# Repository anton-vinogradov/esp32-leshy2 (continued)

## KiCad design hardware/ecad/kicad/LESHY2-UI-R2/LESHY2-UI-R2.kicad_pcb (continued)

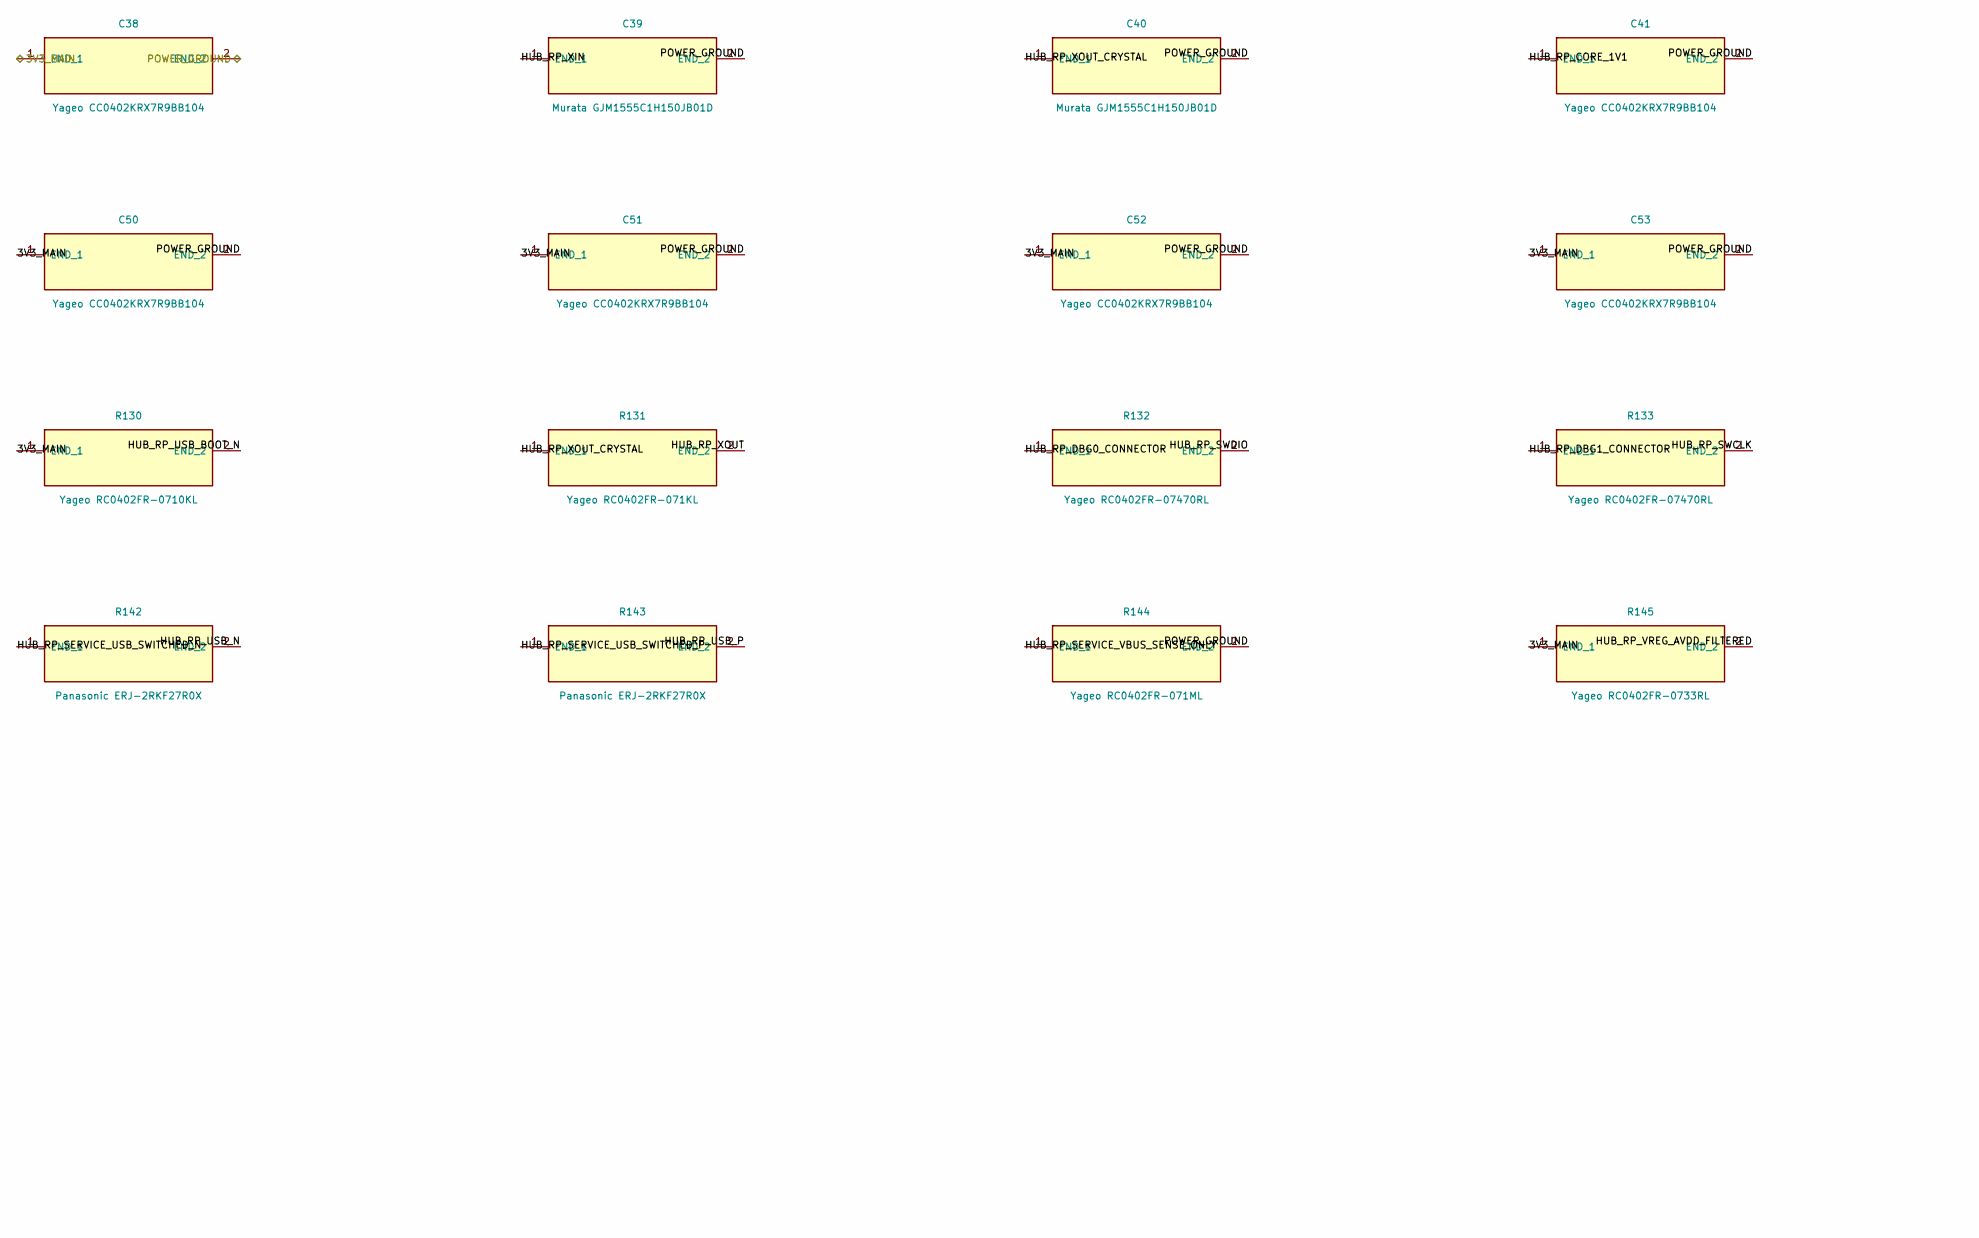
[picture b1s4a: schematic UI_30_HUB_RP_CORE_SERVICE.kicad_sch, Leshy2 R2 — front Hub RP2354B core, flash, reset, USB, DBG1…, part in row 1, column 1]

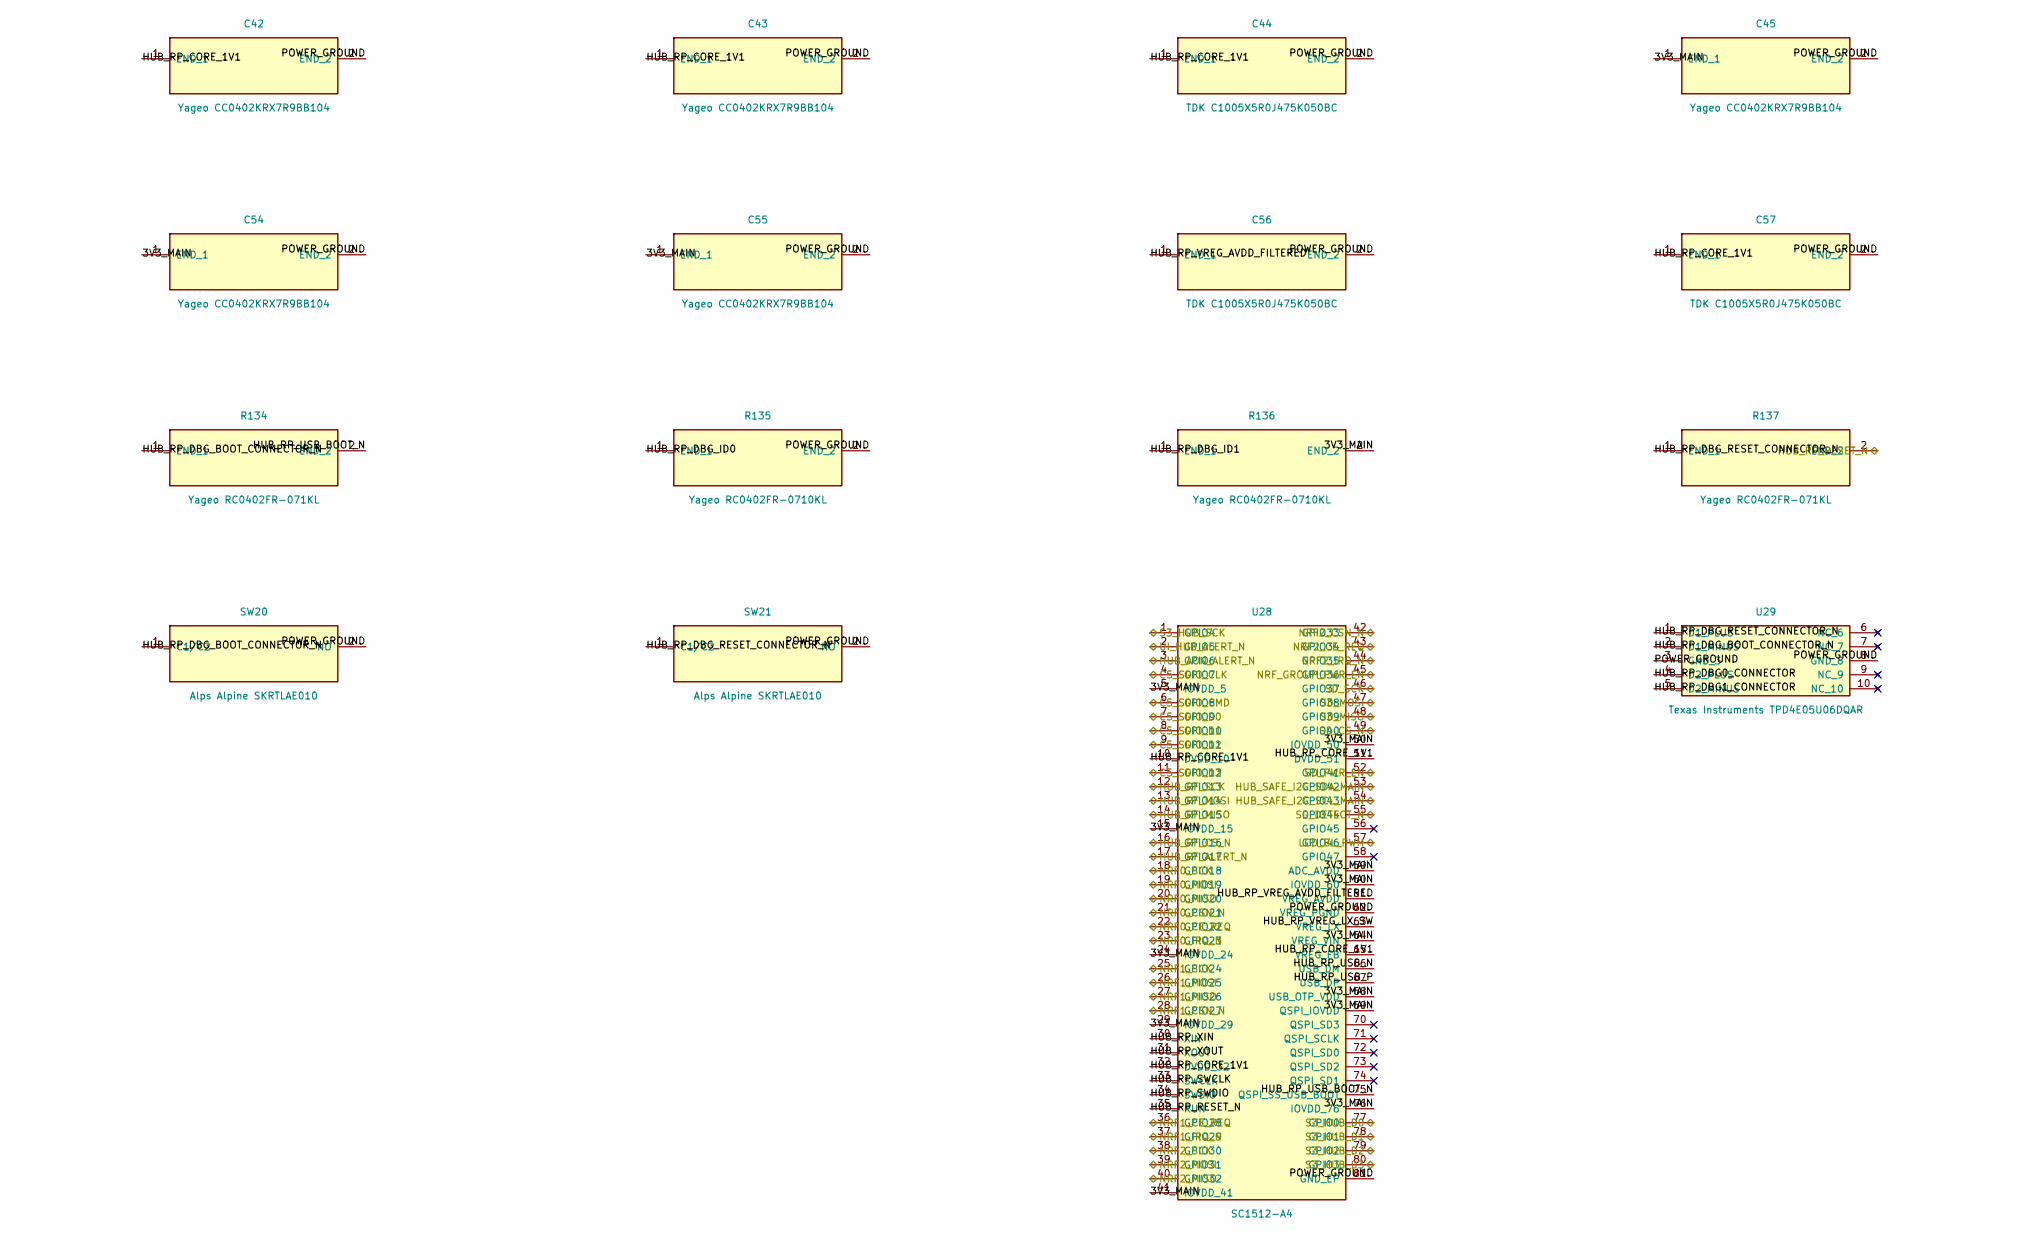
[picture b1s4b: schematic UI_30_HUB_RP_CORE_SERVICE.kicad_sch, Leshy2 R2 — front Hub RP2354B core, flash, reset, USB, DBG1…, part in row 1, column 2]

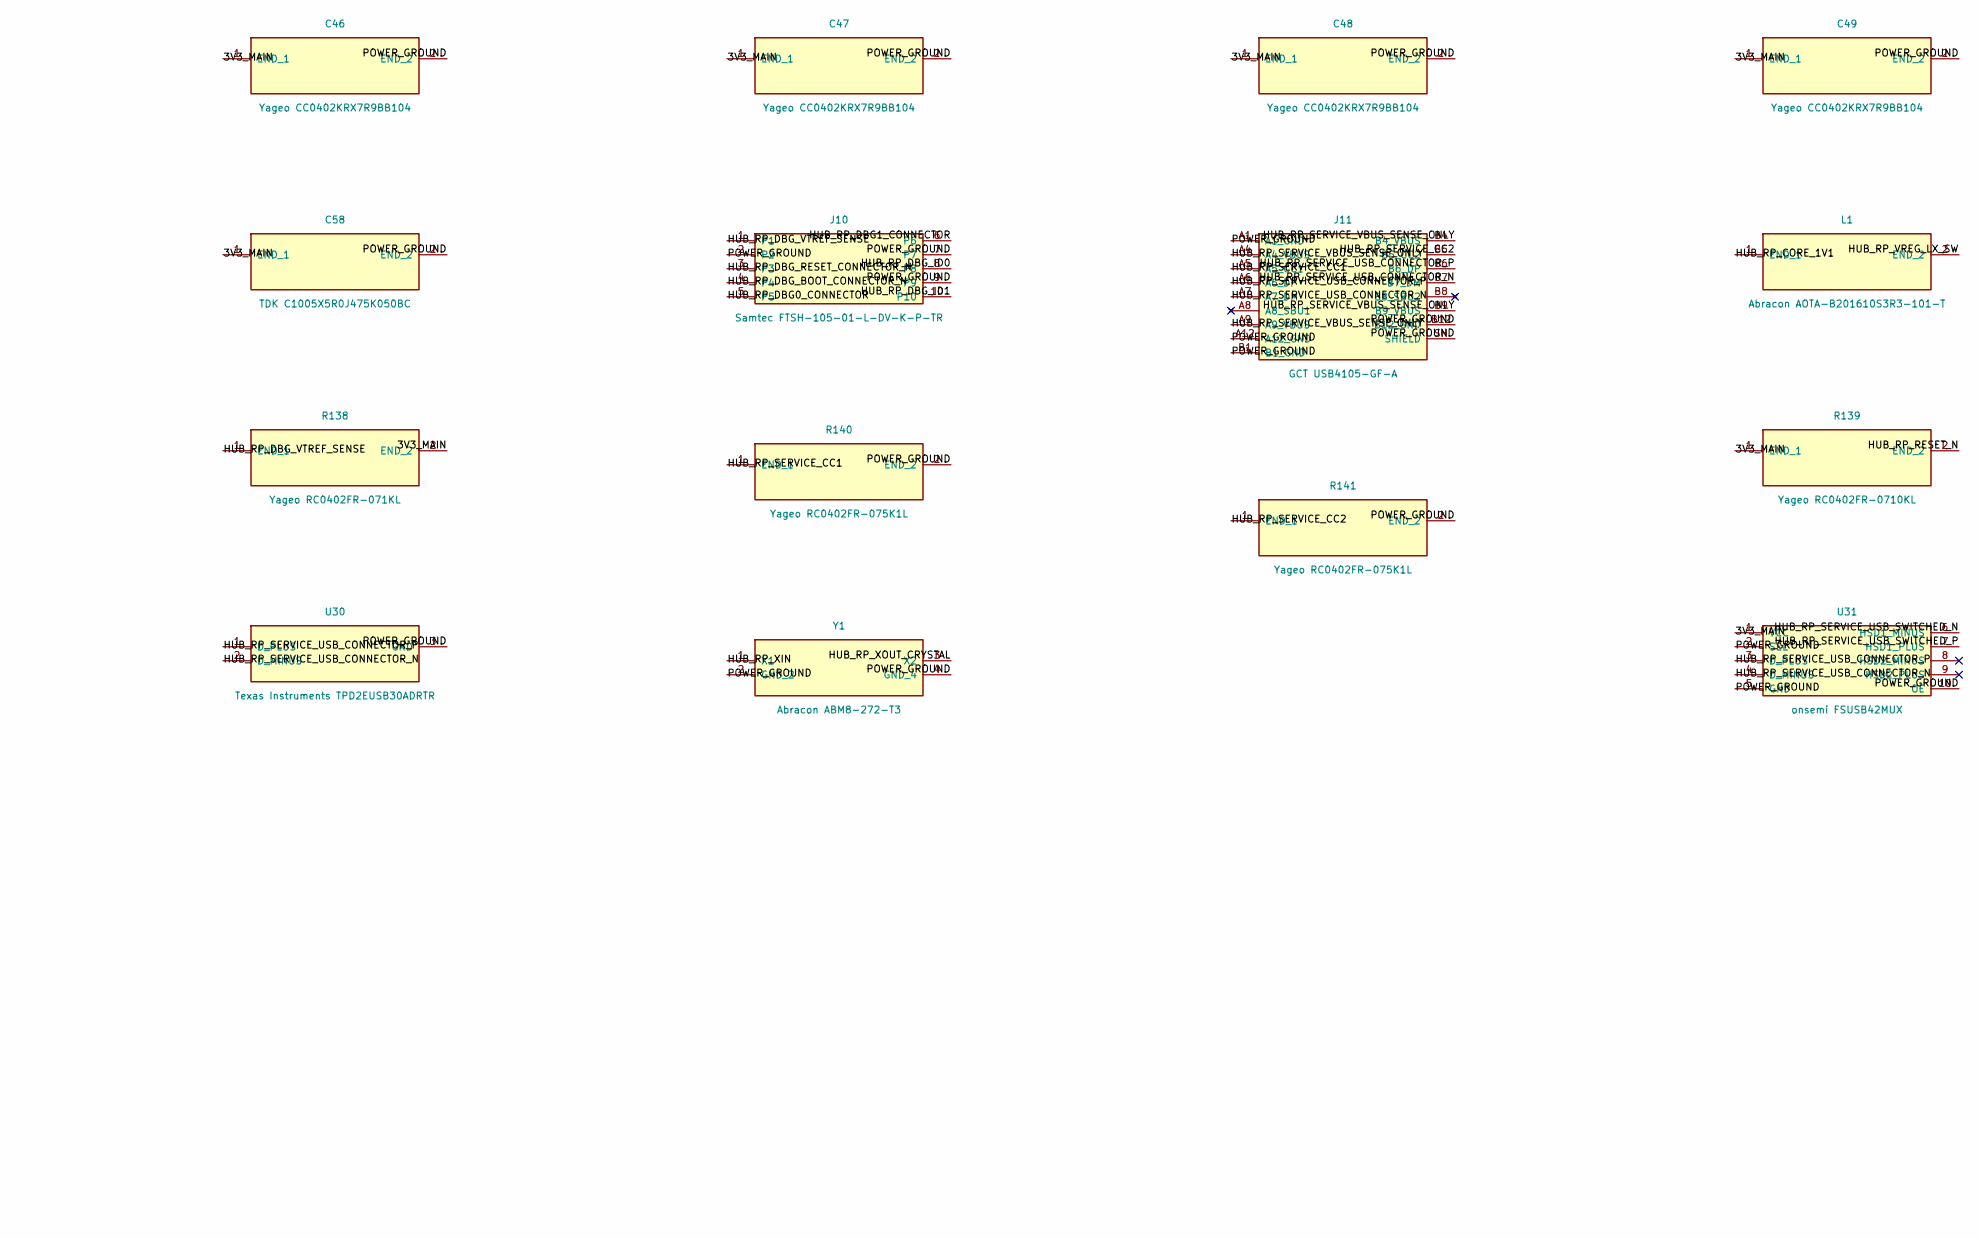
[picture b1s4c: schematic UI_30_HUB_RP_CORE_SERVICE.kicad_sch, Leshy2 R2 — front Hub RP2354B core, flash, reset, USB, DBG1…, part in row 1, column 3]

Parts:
C38, C41, C42, C43, C45, C46, C47, C48, C49, C50, C51, C52, C53, C54, C55: Yageo CC0402KRX7R9BB104; C_0402_1005Metric
C39, C40: Murata GJM1555C1H150JB01D; C_0402_1005Metric
C44, C56, C57, C58: TDK C1005X5R0J475K050BC; C_0402_1005Metric
J10: Samtec FTSH-105-01-L-DV-K-P-TR; FTSH-105-01-L-DV-K-P-TR
J11: GCT USB4105-GF-A; USB_C_Receptacle_GCT_USB4105-xx-A_16P_TopMnt_Horizontal
L1: Abracon AOTA-B201610S3R3-101-T; L_Murata_DFE201610P
R130, R135, R136, R139: Yageo RC0402FR-0710KL; R_0402_1005Metric
R131, R134, R137, R138: Yageo RC0402FR-071KL; R_0402_1005Metric
R132, R133: Yageo RC0402FR-07470RL; R_0402_1005Metric
R140, R141: Yageo RC0402FR-075K1L; R_0402_1005Metric
R142, R143: Panasonic ERJ-2RKF27R0X; R_0402_1005Metric
R144: Yageo RC0402FR-071ML; R_0402_1005Metric
R145: Yageo RC0402FR-0733RL; R_0402_1005Metric
SW20, SW21: Alps Alpine SKRTLAE010; SW_Push_1P1T-MP_NO_Horizontal_Alps_SKRTLAE010
U28: SC1512-A4; QFN-80-1EP_10x10mm_P0.4mm_EP3.4x3.4mm
U29: Texas Instruments TPD4E05U06DQAR; USON-10_2.5x1.0mm_P0.5mm
U30: Texas Instruments TPD2EUSB30ADRTR; Texas_DRT-3
U31: onsemi FSUSB42MUX; MSOP-10_3x3mm_P0.5mm
Y1: Abracon ABM8-272-T3; Crystal_SMD_Abracon_ABM8G-4Pin_3.2x2.5mm

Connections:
/UI_10_S3_DISPLAY_TOUCH/3V3_MAIN: C38.1 (END_1), C45.1 (END_1), C46.1 (END_1), C47.1 (END_1), C48.1 (END_1), C49.1 (END_1), C50.1 (END_1), C51.1 (END_1), C52.1 (END_1), C53.1 (END_1), C54.1 (END_1), C55.1 (END_1), C58.1 (END_1), R130.1 (END_1), R136.2 (END_2), R138.2 (END_2), R139.1 (END_1), R145.1 (END_1), U28.5 (IOVDD_5), U28.15 (IOVDD_15), U28.24 (IOVDD_24), U28.29 (IOVDD_29), U28.41 (IOVDD_41), U28.50 (IOVDD_50), U28.59 (ADC_AVDD), U28.60 (IOVDD_60), U28.64 (VREG_VIN), U28.68 (USB_OTP_VDD), U28.69 (QSPI_IOVDD), U28.76 (IOVDD_76), U31.1 (VCC); also elsewhere on the board
/UI_10_S3_DISPLAY_TOUCH/POWER_GROUND: C38.2 (END_2), C39.2 (END_2), C40.2 (END_2), C41.2 (END_2), C42.2 (END_2), C43.2 (END_2), C44.2 (END_2), C45.2 (END_2), C46.2 (END_2), C47.2 (END_2), C48.2 (END_2), C49.2 (END_2), C50.2 (END_2), C51.2 (END_2), C52.2 (END_2), C53.2 (END_2), C54.2 (END_2), C55.2 (END_2), C56.2 (END_2), C57.2 (END_2), C58.2 (END_2), J10.2, J10.7, J10.9, J11.A1 (A1_GND), J11.A12 (A12_GND), J11.B1 (B1_GND), J11.B12 (B12_GND), J11.SH (SHIELD), R135.2 (END_2), R140.2 (END_2), R141.2 (END_2), R144.2 (END_2), SW20.2 (NO), SW21.2 (NO), U28.62 (VREG_PGND), U28.81 (GND_EP), U29.3 (GND_3), U29.8 (GND_8), U30.3 (GND), U31.2 (SEL), U31.5 (GND), U31.10 (OE), Y1.2 (GND_2), Y1.4 (GND_4); also elsewhere on the board
/UI_10_S3_DISPLAY_TOUCH/S3_HUB_D0: U28.77 (GPIO0); also elsewhere on the board
/UI_10_S3_DISPLAY_TOUCH/S3_HUB_D1: U28.78 (GPIO1); also elsewhere on the board
/UI_10_S3_DISPLAY_TOUCH/S3_HUB_D2: U28.79 (GPIO2); also elsewhere on the board
/UI_10_S3_DISPLAY_TOUCH/S3_HUB_D3: U28.80 (GPIO3); also elsewhere on the board
/UI_10_S3_DISPLAY_TOUCH/S3_HUB_SCK: U28.1 (GPIO4); also elsewhere on the board
/UI_10_S3_DISPLAY_TOUCH/UI_HUB_ALERT_N: U28.2 (GPIO5); also elsewhere on the board
/UI_11_STORAGE_CONTROLS_INDICATORS/LCD_BL_PWM: U28.57 (GPIO46); also elsewhere on the board
/UI_11_STORAGE_CONTROLS_INDICATORS/SD_CS_N: U28.49 (GPIO40); also elsewhere on the board
/UI_11_STORAGE_CONTROLS_INDICATORS/SD_DETECT_N: U28.55 (GPIO44); also elsewhere on the board
/UI_11_STORAGE_CONTROLS_INDICATORS/SD_MISO: U28.48 (GPIO39); also elsewhere on the board
/UI_11_STORAGE_CONTROLS_INDICATORS/SD_MOSI: U28.47 (GPIO38); also elsewhere on the board
/UI_11_STORAGE_CONTROLS_INDICATORS/SD_PWR_EN: U28.52 (GPIO41); also elsewhere on the board
/UI_11_STORAGE_CONTROLS_INDICATORS/SD_SCK: U28.46 (GPIO37); also elsewhere on the board
/UI_20_C5_WIFI_IR_SERVICE/C5_SDIO_CLK: U28.4 (GPIO7); also elsewhere on the board
/UI_20_C5_WIFI_IR_SERVICE/C5_SDIO_CMD: U28.6 (GPIO8); also elsewhere on the board
/UI_20_C5_WIFI_IR_SERVICE/C5_SDIO_D0: U28.7 (GPIO9); also elsewhere on the board
/UI_20_C5_WIFI_IR_SERVICE/C5_SDIO_D1: U28.8 (GPIO10); also elsewhere on the board
/UI_20_C5_WIFI_IR_SERVICE/C5_SDIO_D2: U28.9 (GPIO11); also elsewhere on the board
/UI_20_C5_WIFI_IR_SERVICE/C5_SDIO_D3: U28.11 (GPIO12); also elsewhere on the board
/UI_20_C5_WIFI_IR_SERVICE/HUB_RP_RESET_N: R137.2 (END_2), R139.2 (END_2), U28.35 (RUN); also elsewhere on the board
/UI_30_HUB_RP_CORE_SERVICE/HUB_AON_ALERT_N: U28.3 (GPIO6); also elsewhere on the board
/UI_30_HUB_RP_CORE_SERVICE/HUB_RF_ALERT_N: U28.17 (GPIO17); also elsewhere on the board
/UI_30_HUB_RP_CORE_SERVICE/HUB_RF_CS_N: U28.16 (GPIO16); also elsewhere on the board
/UI_30_HUB_RP_CORE_SERVICE/HUB_RF_MISO: U28.14 (GPIO15); also elsewhere on the board
/UI_30_HUB_RP_CORE_SERVICE/HUB_RF_MOSI: U28.13 (GPIO14); also elsewhere on the board
/UI_30_HUB_RP_CORE_SERVICE/HUB_RF_SCK: U28.12 (GPIO13); also elsewhere on the board
/UI_30_HUB_RP_CORE_SERVICE/HUB_RP_CORE_1V1: C41.1 (END_1), C42.1 (END_1), C43.1 (END_1), C44.1 (END_1), C57.1 (END_1), L1.1 (END_1), U28.10 (DVDD_10), U28.32 (DVDD_32), U28.51 (DVDD_51), U28.65 (VREG_FB)
/UI_30_HUB_RP_CORE_SERVICE/HUB_RP_DBG0_CONNECTOR: J10.5, R132.1 (END_1), U29.4 (D2_PLUS)
/UI_30_HUB_RP_CORE_SERVICE/HUB_RP_DBG1_CONNECTOR: J10.6, R133.1 (END_1), U29.5 (D2_MINUS)
/UI_30_HUB_RP_CORE_SERVICE/HUB_RP_DBG_BOOT_CONNECTOR_N: J10.4, R134.1 (END_1), SW20.1 (C1/C2), U29.2 (D1_MINUS)
/UI_30_HUB_RP_CORE_SERVICE/HUB_RP_DBG_ID0: J10.8, R135.1 (END_1)
/UI_30_HUB_RP_CORE_SERVICE/HUB_RP_DBG_ID1: J10.10, R136.1 (END_1)
/UI_30_HUB_RP_CORE_SERVICE/HUB_RP_DBG_RESET_CONNECTOR_N: J10.3, R137.1 (END_1), SW21.1 (C1/C2), U29.1 (D1_PLUS)
/UI_30_HUB_RP_CORE_SERVICE/HUB_RP_DBG_VTREF_SENSE: J10.1, R138.1 (END_1)
/UI_30_HUB_RP_CORE_SERVICE/HUB_RP_SERVICE_CC1: J11.A5 (A5_CC1), R140.1 (END_1)
/UI_30_HUB_RP_CORE_SERVICE/HUB_RP_SERVICE_CC2: J11.B5 (B5_CC2), R141.1 (END_1)
/UI_30_HUB_RP_CORE_SERVICE/HUB_RP_SERVICE_USB_CONNECTOR_N: J11.A7 (A7_DM), J11.B7 (B7_DM), U30.2 (D_MINUS), U31.4 (D_MINUS)
/UI_30_HUB_RP_CORE_SERVICE/HUB_RP_SERVICE_USB_CONNECTOR_P: J11.A6 (A6_DP), J11.B6 (B6_DP), U30.1 (D_PLUS), U31.3 (D_PLUS)
/UI_30_HUB_RP_CORE_SERVICE/HUB_RP_SERVICE_USB_SWITCHED_N: R142.1 (END_1), U31.6 (HSD1_MINUS)
/UI_30_HUB_RP_CORE_SERVICE/HUB_RP_SERVICE_USB_SWITCHED_P: R143.1 (END_1), U31.7 (HSD1_PLUS)
/UI_30_HUB_RP_CORE_SERVICE/HUB_RP_SERVICE_VBUS_SENSE_ONLY: J11.A4 (A4_VBUS), J11.A9 (A9_VBUS), J11.B4 (B4_VBUS), J11.B9 (B9_VBUS), R144.1 (END_1)
/UI_30_HUB_RP_CORE_SERVICE/HUB_RP_SWCLK: R133.2 (END_2), U28.33 (SWCLK)
/UI_30_HUB_RP_CORE_SERVICE/HUB_RP_SWDIO: R132.2 (END_2), U28.34 (SWDIO)
/UI_30_HUB_RP_CORE_SERVICE/HUB_RP_USB_BOOT_N: R130.2 (END_2), R134.2 (END_2), U28.75 (QSPI_SS_USB_BOOT)
/UI_30_HUB_RP_CORE_SERVICE/HUB_RP_USB_N: R142.2 (END_2), U28.66 (USB_DM)
/UI_30_HUB_RP_CORE_SERVICE/HUB_RP_USB_P: R143.2 (END_2), U28.67 (USB_DP)
/UI_30_HUB_RP_CORE_SERVICE/HUB_RP_VREG_AVDD_FILTERED: C56.1 (END_1), R145.2 (END_2), U28.61 (VREG_AVDD)
/UI_30_HUB_RP_CORE_SERVICE/HUB_RP_VREG_LX_SW: L1.2 (END_2), U28.63 (VREG_LX)
/UI_30_HUB_RP_CORE_SERVICE/HUB_RP_XIN: C39.1 (END_1), U28.30 (XIN), Y1.1 (X1)
/UI_30_HUB_RP_CORE_SERVICE/HUB_RP_XOUT: R131.2 (END_2), U28.31 (XOUT)
/UI_30_HUB_RP_CORE_SERVICE/HUB_RP_XOUT_CRYSTAL: C40.1 (END_1), R131.1 (END_1), Y1.3 (X2)
/UI_30_HUB_RP_CORE_SERVICE/HUB_SAFE_I2C_SCL_MAIN: U28.54 (GPIO43); also elsewhere on the board
/UI_30_HUB_RP_CORE_SERVICE/HUB_SAFE_I2C_SDA_MAIN: U28.53 (GPIO42); also elsewhere on the board
/UI_30_HUB_RP_CORE_SERVICE/NRF0_CE_REQ: U28.22 (GPIO22); also elsewhere on the board
/UI_30_HUB_RP_CORE_SERVICE/NRF1_CE_REQ: U28.36 (GPIO28); also elsewhere on the board
/UI_30_HUB_RP_CORE_SERVICE/NRF2_CE_REQ: U28.43 (GPIO34); also elsewhere on the board
/UI_30_HUB_RP_CORE_SERVICE/NRF_GROUP_PWR_EN: U28.45 (GPIO36); also elsewhere on the board
/UI_31_NRF24_X3_TX_EVIDENCE/NRF0_CSN_N: U28.21 (GPIO21); also elsewhere on the board
/UI_31_NRF24_X3_TX_EVIDENCE/NRF0_IRQ_N: U28.23 (GPIO23); also elsewhere on the board
/UI_31_NRF24_X3_TX_EVIDENCE/NRF0_MISO: U28.20 (GPIO20); also elsewhere on the board
/UI_31_NRF24_X3_TX_EVIDENCE/NRF0_MOSI: U28.19 (GPIO19); also elsewhere on the board
/UI_31_NRF24_X3_TX_EVIDENCE/NRF0_SCK: U28.18 (GPIO18); also elsewhere on the board
/UI_31_NRF24_X3_TX_EVIDENCE/NRF1_CSN_N: U28.28 (GPIO27); also elsewhere on the board
/UI_31_NRF24_X3_TX_EVIDENCE/NRF1_IRQ_N: U28.37 (GPIO29); also elsewhere on the board
/UI_31_NRF24_X3_TX_EVIDENCE/NRF1_MISO: U28.27 (GPIO26); also elsewhere on the board
/UI_31_NRF24_X3_TX_EVIDENCE/NRF1_MOSI: U28.26 (GPIO25); also elsewhere on the board
/UI_31_NRF24_X3_TX_EVIDENCE/NRF1_SCK: U28.25 (GPIO24); also elsewhere on the board
/UI_31_NRF24_X3_TX_EVIDENCE/NRF2_CSN_N: U28.42 (GPIO33); also elsewhere on the board
/UI_31_NRF24_X3_TX_EVIDENCE/NRF2_IRQ_N: U28.44 (GPIO35); also elsewhere on the board
/UI_31_NRF24_X3_TX_EVIDENCE/NRF2_MISO: U28.40 (GPIO32); also elsewhere on the board
/UI_31_NRF24_X3_TX_EVIDENCE/NRF2_MOSI: U28.39 (GPIO31); also elsewhere on the board
/UI_31_NRF24_X3_TX_EVIDENCE/NRF2_SCK: U28.38 (GPIO30); also elsewhere on the board
